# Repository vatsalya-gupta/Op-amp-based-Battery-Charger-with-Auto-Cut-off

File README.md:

# Op-amp based Battery Charger Circuit with Auto Cut-off

The project proposes a two op-amp based auto cut off battery charger circuit which is not only accurate with its features but also allows a hassle free and quick setting up of its high/low cut-off threshold limits. The major objectives include:

1. To design a circuit which will automatically disconnect the battery and supply power to the system, when the circuit is connected to an external power source, in the meanwhile also charging the battery.
2. Overcharging protection for the battery.
3. Battery low and full charging indications.

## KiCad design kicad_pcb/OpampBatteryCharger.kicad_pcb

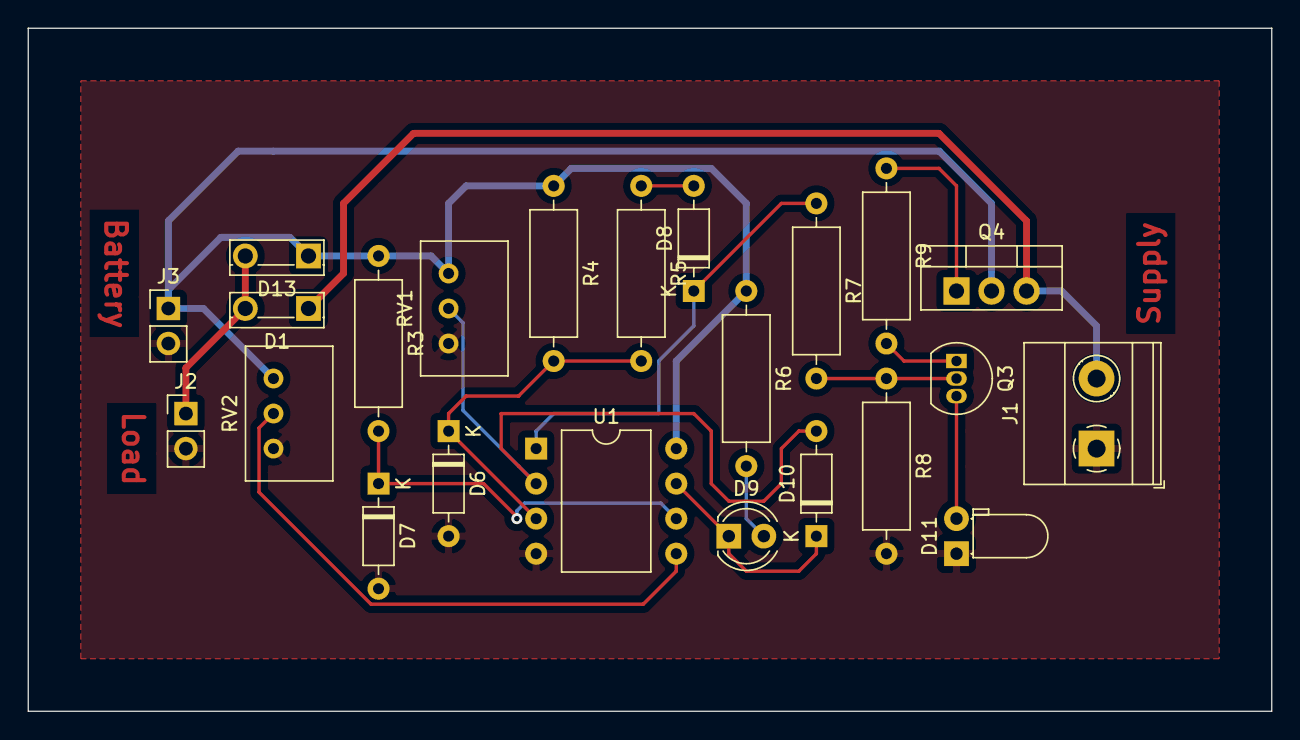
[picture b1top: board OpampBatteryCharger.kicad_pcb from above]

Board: 2 copper layers, 90.2 x 49.5 mm, 23 parts (0 on the bottom side), 16 nets.

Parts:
D1, D13: RRE02V545; TO-251-2_Vertical
D6, D7: 1N750; D_DO-35_SOD27_P7.62mm_Horizontal
D8, D10: 1N4148; D_DO-35_SOD27_P7.62mm_Horizontal
D9: LED; LED_D4.0mm
D11: LED; LED_D3.0mm_Horizontal_O1.27mm_Z2.0mm
J1: Supply; TerminalBlock_Phoenix_MKDS-1,5-2-5.08_1x02_P5.08mm_Horizont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
J2: Load; PinHeader_1x02_P2.54mm_Vertical
J3: Battery; PinHeader_1x02_P2.54mm_Vertical
Q3: BC547; TO-92_Inline
Q4: TIP32; TO-220-3_Vertical
R3, R4, R5, R6, R7, R8, R9: R; R_Axial_DIN0309_L9.0mm_D3.2mm_P12.70mm_Horizontal
RV1, RV2: R_POT_TRIM; Potentiometer_Bourns_3299W_Vertical
U1: LM358; DIP-8_W10.16mm

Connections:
Battery+: D13.1, J3.1, Q4.2, R3.1, R4.1, R6.1, RV1.1, RV2.1, U1.8
Battery-: D6.2, D7.2, D11.1, J1.1, J2.2, J3.2, R8.2, RV1.3, RV2.3, U1.4
Load+: D1.2, D13.2, J2.1
unnamed: D6.1, R4.2, R5.2, U1.3
unnamed: D7.1, R3.2, U1.6
unnamed: D8.1, R7.1, U1.1
unnamed: D8.2, R5.1
unnamed: D9.2, R6.2
unnamed: D9.1, D10.1, U1.7
unnamed: D10.2, RV1.2, U1.2
unnamed: D11.2, Q3.3
unnamed: Q3.1, R9.2
unnamed: Q3.2, R7.2, R8.1
unnamed: Q4.1, R9.1
unnamed: RV2.2, U1.5
Supply+: D1.1, J1.2, Q4.3
